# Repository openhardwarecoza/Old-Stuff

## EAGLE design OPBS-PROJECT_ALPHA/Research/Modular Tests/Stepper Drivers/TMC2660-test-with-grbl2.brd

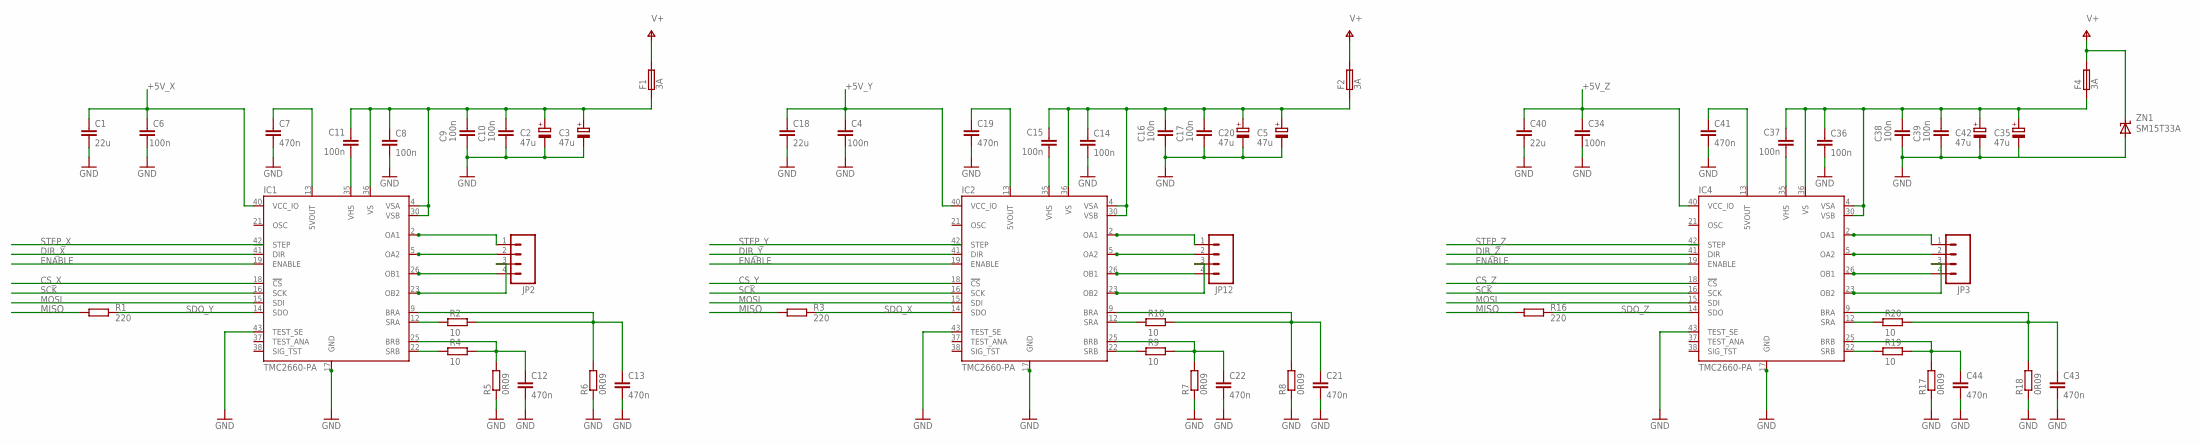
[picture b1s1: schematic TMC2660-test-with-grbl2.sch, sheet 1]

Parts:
C1, C18, C40: 22u; C1206; VOLTAGE 6.3V; PARTNR JMK316B7226ML-T
C2, C3, C5, C20, C35, C42: 47u; E5-8,5; VOLTAGE 50V; PARTNR EEEFK1H470XP
C4, C6, C34: 100n; C1206K; VOLTAGE 25V; PARTNR C0603C104K3RACTU
C7, C12, C13, C19, C21, C22, C41, C43, C44: 470n; 0805-WIDE; VOLTAGE 10V; PARTNR VJ0805Y474KXQTW1BC
C8, C9, C10, C11, C14, C15, C16, C17, C36, C37, C38, C39: 100n; C0603K; VOLTAGE 50V; PARTNR C0603C104K5RACTU
F1, F2, F4: 3A; AF2; VOLTAGE 125V; PARTNR CB61F3A-TR2
IC1, IC2, IC4: TMC2660-PA; PQFP44; PARTNR TMC2660
JP2, JP3, JP12: M04SCREW; SCREWTERMINAL-3.5MM-4
R1, R3, R16: 220; R0603; PARTNR SG73S1JTTD221J
R2, R4, R9, R10, R19, R20: 10; R0603; PARTNR RN73H1JTTD10R0F100
R5, R6, R7, R8, R17, R18: 0R09; R1206; PARTNR ERJ-B2CFR091V
ZN1: SM15T33A; SMC; PARTNR SM15T33A

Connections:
+5V_X: C1.1, C6.2, IC1.40 (VCC_IO)
+5V_Y: C4.2, C18.1, IC2.40 (VCC_IO)
+5V_Z: C34.2, C40.1, IC4.40 (VCC_IO)
CS_X: IC1.18 (!CS); also elsewhere on the board
CS_Y: IC2.18 (!CS); also elsewhere on the board
CS_Z: IC4.18 (!CS); also elsewhere on the board
DIR_X: IC1.41 (DIR); also elsewhere on the board
DIR_Y: IC2.41 (DIR); also elsewhere on the board
DIR_Z: IC4.41 (DIR); also elsewhere on the board
ENABLE: IC1.19 (ENABLE), IC2.19 (ENABLE), IC4.19 (ENABLE)
GND: C1.2, C2.-, C3.-, C4.1, C5.-, C6.1, C7.2, C8.2, C9.1, C10.1, C12.2, C13.2, C14.2, C16.1, C17.1, C18.2, C19.2, C20.-, C21.2, C22.2, C34.1, C35.-, C36.2, C38.1, C39.1, C40.2, C41.2, C42.-, C43.2, C44.2, IC1.17 (GND), IC1.39 (GND1), IC1.43 (TEST_SE), IC1.44 (GND2), IC2.17 (GND), IC2.39 (GND1), IC2.43 (TEST_SE), IC2.44 (GND2), IC4.17 (GND), IC4.39 (GND1), IC4.43 (TEST_SE), IC4.44 (GND2), R5.1, R6.1, R7.1, R8.1, R17.1, R18.1, ZN1.P$2 (A); also elsewhere on the board
MISO: R1.2, R3.2, R16.2; also elsewhere on the board
MOSI: IC1.15 (SDI), IC2.15 (SDI), IC4.15 (SDI); also elsewhere on the board
unnamed: IC1.22 (SRB), R4.2
unnamed: C12.1, IC1.25 (BRB), R4.1, R5.2
unnamed: C13.1, IC1.9 (BRA), R2.1, R6.2
unnamed: IC1.12 (SRA), R2.2
unnamed: C22.1, IC2.25 (BRB), R7.2, R9.1
unnamed: C21.1, IC2.9 (BRA), R8.2, R10.1
unnamed: IC2.22 (SRB), R9.2
unnamed: IC2.12 (SRA), R10.2
unnamed: C44.1, IC4.25 (BRB), R17.2, R19.1
unnamed: C43.1, IC4.9 (BRA), R18.2, R20.1
unnamed: IC4.22 (SRB), R19.2
unnamed: IC4.12 (SRA), R20.2
OA1: IC1.2 (OA1), IC1.3 (OA1_1), IC1.7 (OA1_2), IC1.8 (OA1_3), JP2.1
OA2: IC1.5 (OA2), IC1.6 (OA2_1), IC1.10 (OA2_2), IC1.11 (OA2_3), JP2.2
OA3: IC2.2 (OA1), IC2.3 (OA1_1), IC2.7 (OA1_2), IC2.8 (OA1_3), JP12.1
OA4: IC2.5 (OA2), IC2.6 (OA2_1), IC2.10 (OA2_2), IC2.11 (OA2_3), JP12.2
OA5: IC4.2 (OA1), IC4.3 (OA1_1), IC4.7 (OA1_2), IC4.8 (OA1_3), JP3.1
OA6: IC4.5 (OA2), IC4.6 (OA2_1), IC4.10 (OA2_2), IC4.11 (OA2_3), JP3.2
OB1: IC1.26 (OB1), IC1.27 (OB1_1), IC1.31 (OB1_2), IC1.32 (OB1_3), JP2.4
OB2: IC1.23 (OB2), IC1.24 (OB2_1), IC1.28 (OB2_2), IC1.29 (OB2_3), JP2.3
OB3: IC2.23 (OB2), IC2.24 (OB2_1), IC2.28 (OB2_2), IC2.29 (OB2_3), JP12.3
OB4: IC2.26 (OB1), IC2.27 (OB1_1), IC2.31 (OB1_2), IC2.32 (OB1_3), JP12.4
OB5: IC4.23 (OB2), IC4.24 (OB2_1), IC4.28 (OB2_2), IC4.29 (OB2_3), JP3.3
OB6: IC4.26 (OB1), IC4.27 (OB1_1), IC4.31 (OB1_2), IC4.32 (OB1_3), JP3.4
PWR_X: C2.+, C3.+, C8.1, C9.2, C10.2, C11.2, F1.P$1 (1), IC1.4 (VSA), IC1.30 (VSB), IC1.36 (VS)
PWR_Y: C5.+, C14.1, C15.2, C16.2, C17.2, C20.+, F2.P$1 (1), IC2.4 (VSA), IC2.30 (VSB), IC2.36 (VS)
PWR_Z: C35.+, C36.1, C37.2, C38.2, C39.2, C42.+, F4.P$1 (1), IC4.4 (VSA), IC4.30 (VSB), IC4.36 (VS)
SCK: IC1.16 (SCK), IC2.16 (SCK), IC4.16 (SCK); also elsewhere on the board
SDO_X: IC2.14 (SDO), R3.1
SDO_Y: IC1.14 (SDO), R1.1
SDO_Z: IC4.14 (SDO), R16.1
STEP_X: IC1.42 (STEP); also elsewhere on the board
STEP_Y: IC2.42 (STEP); also elsewhere on the board
STEP_Z: IC4.42 (STEP); also elsewhere on the board
V+: F1.P$2 (2), F2.P$2 (2), F4.P$2 (2), ZN1.P$1 (C); also elsewhere on the board
VHS: C11.1, IC1.35 (VHS)
VHS1: C15.1, IC2.35 (VHS)
VHS2: C37.1, IC4.35 (VHS)
VREG: C7.1, IC1.13 (5VOUT)
VREG1: C19.1, IC2.13 (5VOUT)
VREG2: C41.1, IC4.13 (5VOUT)

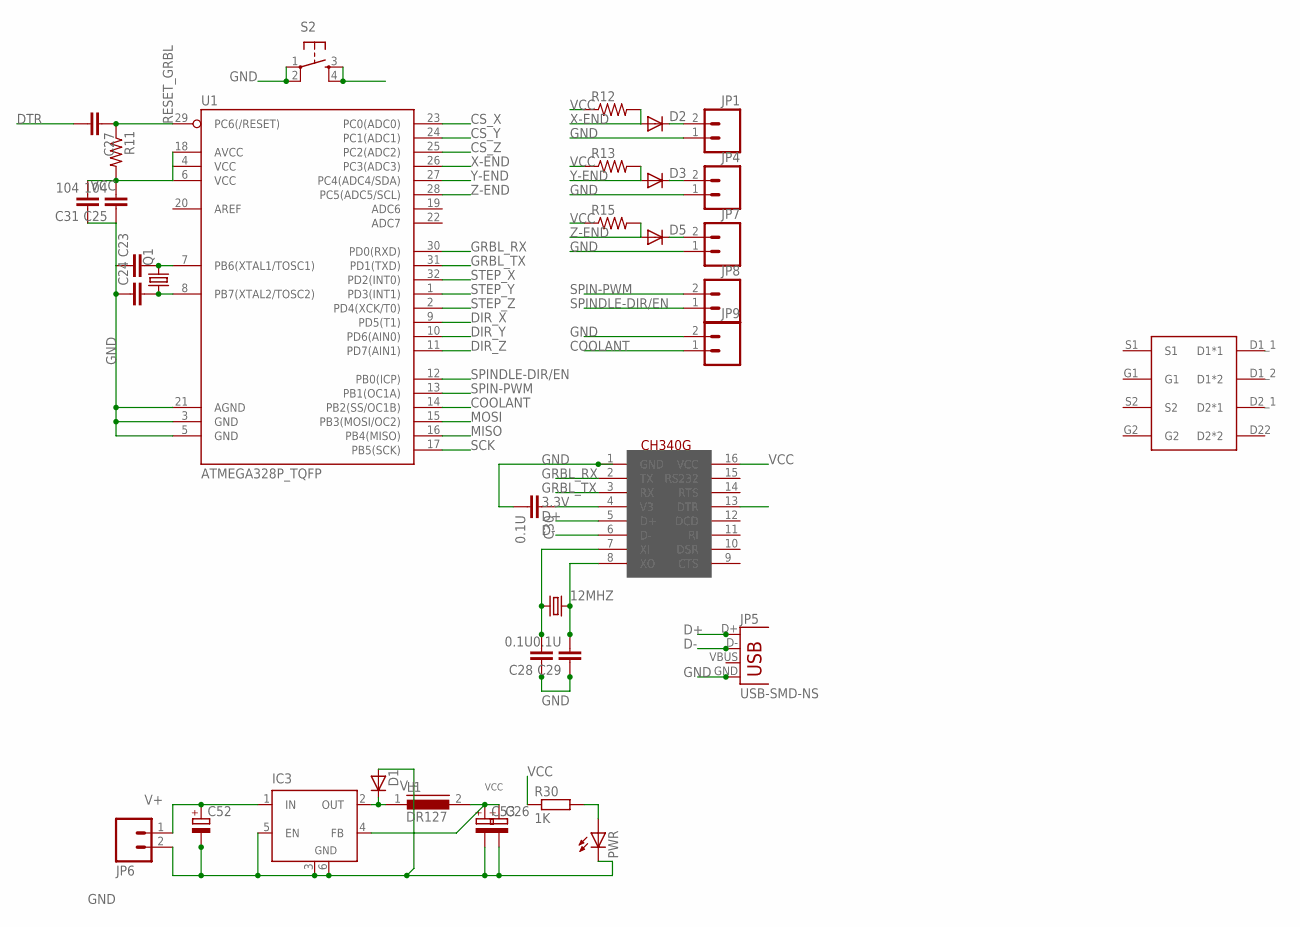
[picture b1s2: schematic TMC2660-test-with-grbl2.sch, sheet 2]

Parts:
12MHZ: CRYSTALHC49UP; HC49UP
C23, C24, C27: CAP1206; 1206
C25, C31: 104; 1206
C26: CPOL-EUE2.5-6; E2,5-6
C28, C29, C30: 0.1U; C1206
C52, C53: CPOL-EUE5-8.5; E5-8,5
D1: D-SOD-80; SOD80
D2, D3, D5: DIODESMB; SMB-DIODE
IC3: LM2596S; TO263-5
JP1, JP4, JP6, JP7, JP8, JP9: M023.5MM; SCREWTERMINAL-3.5MM-2
JP5: USB-SMD-NS; USB-MINIB-NOSTOP
L1: DR127
PWR: LEDCHIPLED_1206; CHIPLED_1206
Q1: CRYSTALHC49UP; HC49UP
R11, R12, R13, R15: RESISTOR1206; 1206
R30: 1K; M1206
S2: TAC_SWITCHSMD; TACTILE_SWITCH_SMD
U1: ATMEGA328P_TQFP; TQFP32-08
U$3: CSD88537ND
U$4: CH340G; SOIC16

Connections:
3.3V: C30.1, U$4.4 (V3)
COOLANT: JP9.1, U1.14 (PB2(SS/OC1B))
CS_X: U1.23 (PC0(ADC0)); also elsewhere on the board
CS_Y: U1.24 (PC1(ADC1)); also elsewhere on the board
CS_Z: U1.25 (PC2(ADC2)); also elsewhere on the board
D1*1: U$3.D1_1 (D1*1)
D1*2: U$3.D1_2 (D1*2)
D2*1: U$3.D2_1 (D2*1)
D2*2: U$3.D22 (D2*2)
D+: JP5.D+, U$4.5 (D+)
D-: JP5.D-, U$4.6 (D-)
DIR_X: U1.9 (PD5(T1)); also elsewhere on the board
DIR_Y: U1.10 (PD6(AIN0)); also elsewhere on the board
DIR_Z: U1.11 (PD7(AIN1)); also elsewhere on the board
DTR: C27.2, U$4.13 (DTR)
G1: U$3.G1
G2: U$3.G2
GND: C23.1, C24.1, C25.1, C26.-, C28.1, C29.1, C30.2, C31.1, C52.-, C53.-, D1.2 (A), IC3.3 (GND), IC3.5 (EN), IC3.6 (GND), JP1.1, JP4.1, JP5.GND, JP6.2, JP7.1, JP9.2, PWR.C, S2.1, S2.2, U1.3 (GND), U1.5 (GND), U1.21 (AGND), U$4.1 (GND); also elsewhere on the board
GRBL_RX: U1.30 (PD0(RXD)), U$4.2 (TX)
GRBL_TX: U1.31 (PD1(TXD)), U$4.3 (RX)
MISO: U1.16 (PB4(MISO)); also elsewhere on the board
MOSI: U1.15 (PB3(MOSI/OC2)); also elsewhere on the board
unnamed: C23.2, Q1.2, U1.7 (PB6(XTAL1/TOSC1))
unnamed: C24.2, Q1.1, U1.8 (PB7(XTAL2/TOSC2))
unnamed: D2.C, JP1.2
unnamed: D3.C, JP4.2
unnamed: 12MHZ.1, C28.2, U$4.7 (XI)
unnamed: D5.C, JP7.2
unnamed: 12MHZ.2, C29.2, U$4.8 (XO)
unnamed: D1.1 (C), IC3.2 (OUT), L1.1
unnamed: PWR.A, R30.2
RESET_GRBL: C27.1, R11.1, S2.3, S2.4, U1.29 (PC6(/RESET))
S1: U$3.S1
S2: U$3.S2
SCK: U1.17 (PB5(SCK)); also elsewhere on the board
SPIN-PWM: JP8.2, U1.13 (PB1(OC1A))
SPINDLE-DIR/EN: JP8.1, U1.12 (PB0(ICP))
STEP_X: U1.32 (PD2(INT0)); also elsewhere on the board
STEP_Y: U1.1 (PD3(INT1)); also elsewhere on the board
STEP_Z: U1.2 (PD4(XCK/T0)); also elsewhere on the board
V+: C52.+, IC3.1 (IN), JP6.1; also elsewhere on the board
VCC: C25.2, C26.+, C31.2, C53.+, IC3.4 (FB), L1.2, R11.2, R12.1, R13.1, R15.1, R30.1, U1.4 (VCC), U1.6 (VCC), U1.18 (AVCC), U$4.16 (VCC)
X-END: D2.A, R12.2, U1.26 (PC3(ADC3))
Y-END: D3.A, R13.2, U1.27 (PC4(ADC4/SDA))
Z-END: D5.A, R15.2, U1.28 (PC5(ADC5/SCL))

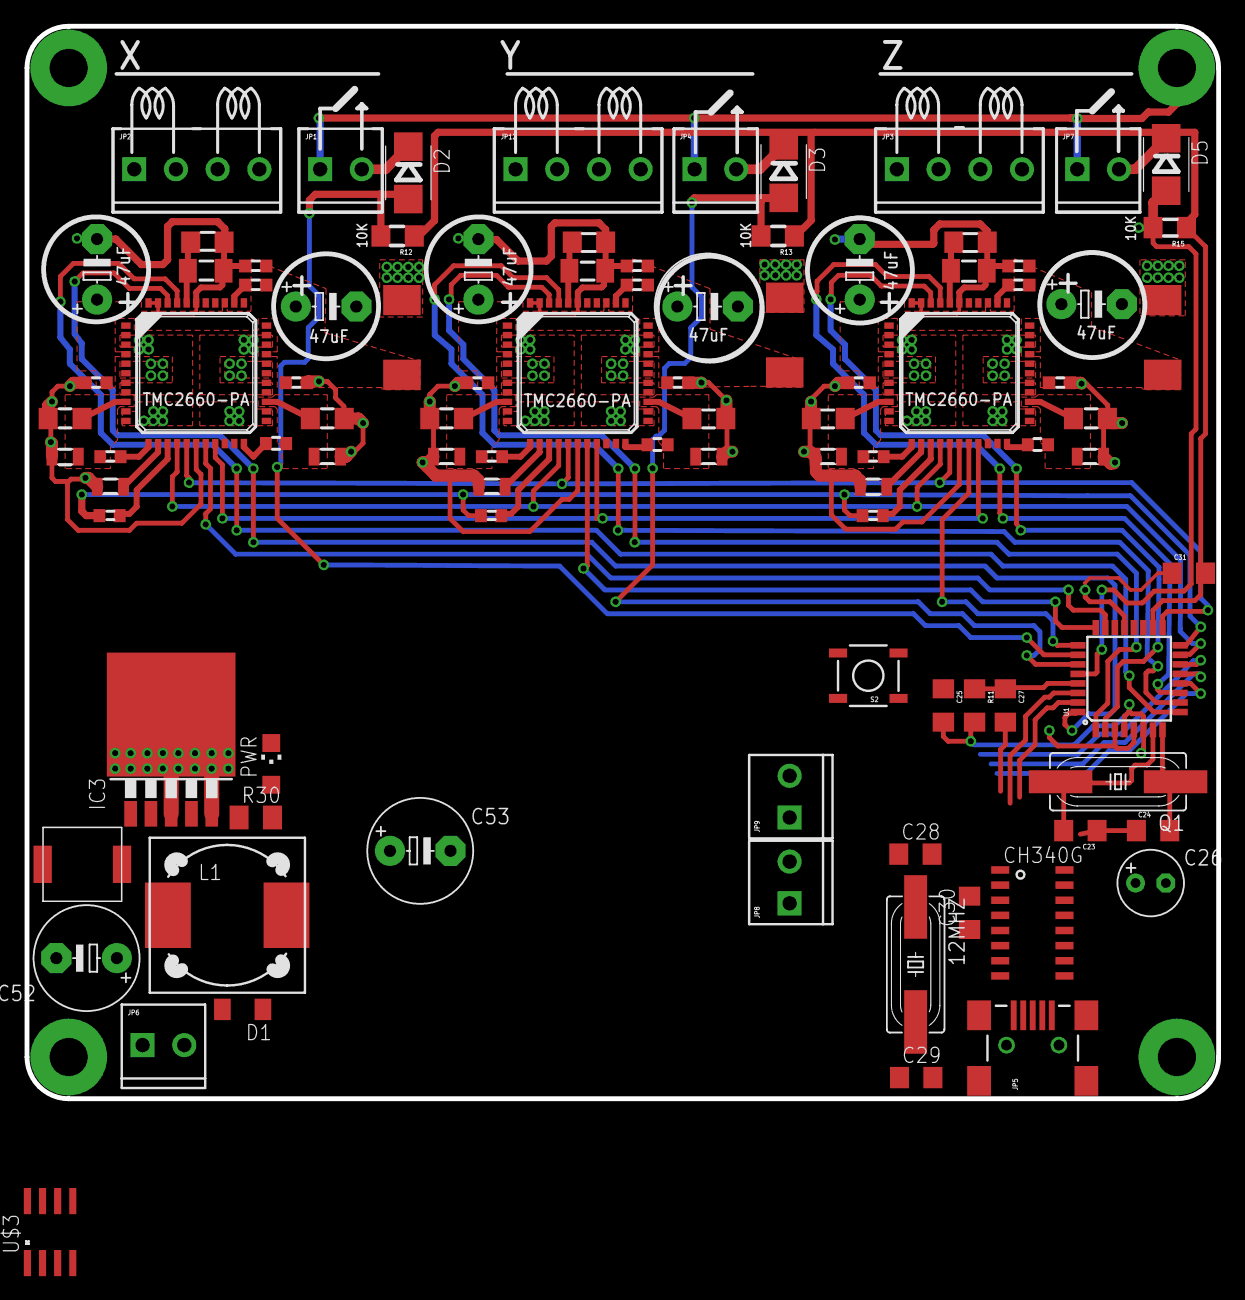
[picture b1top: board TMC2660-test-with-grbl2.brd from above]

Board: 2 copper layers, 100.0 x 90.0 mm, 94 parts (0 on the bottom side), 77 nets.

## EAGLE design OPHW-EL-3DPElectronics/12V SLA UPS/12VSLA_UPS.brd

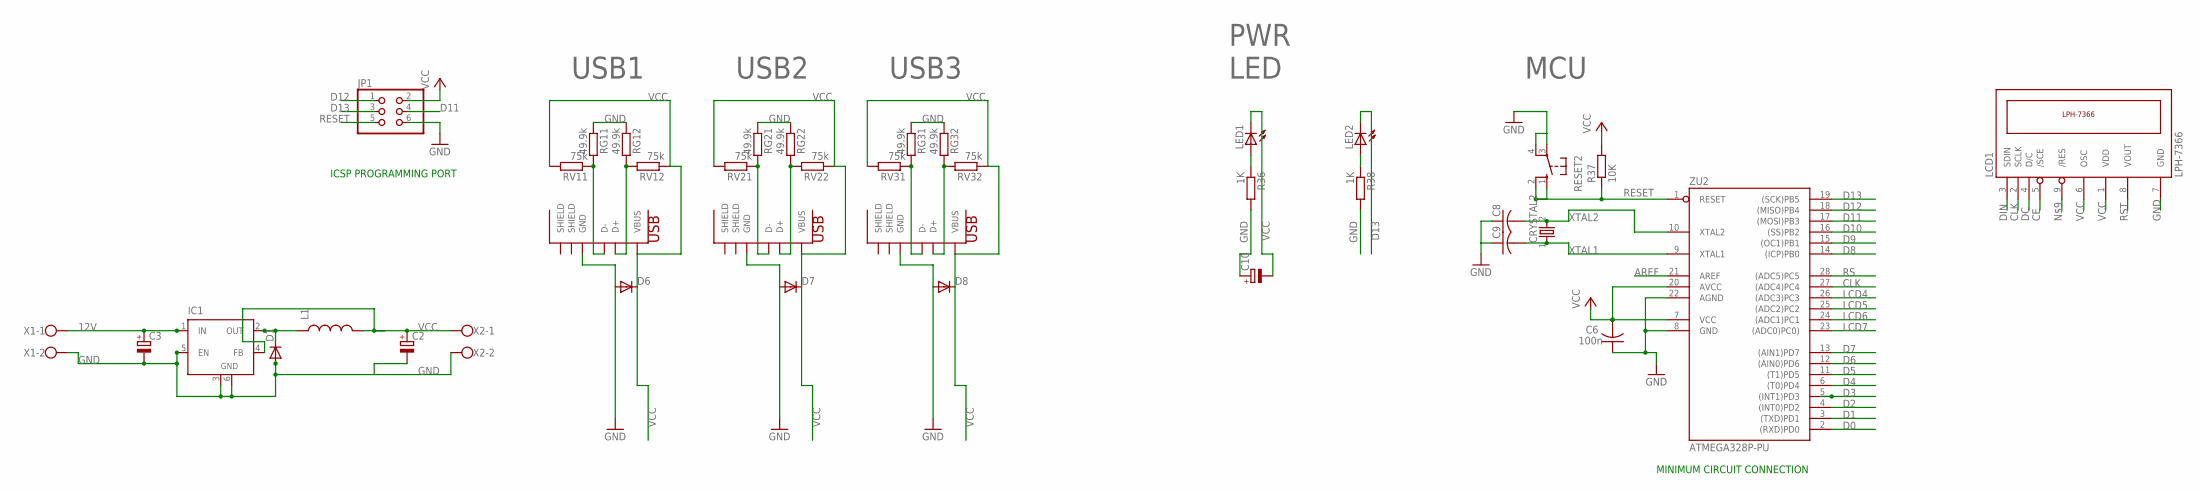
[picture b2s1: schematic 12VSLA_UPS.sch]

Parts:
C2, C3: CPOL-EU153CLV-0605; 153CLV-0605
C6: 100n; C1206K
C8, C9: C-USC1206K; C1206K
C10: CPOL-EU153CLV-0807; 153CLV-0807
CRYSTAL2: CRYSTAL2PIN; CRYSTAL-2PIN
D1: DIODE-DO-214AC; DO-214AC
D6, D7, D8: DIODESMA-ALT; SMA-DIODE_ALT
IC1: LM2596S; TO263-5
JP1: PINHD-2X3; 2X03
L1: INDUCTORPWR; CDRH125
LCD1: LPH-7366
LED1, LED2: LED3MM
R36, R38: 1K; M1206
R37: 10K; M1206
RESET2: 10-XX; B3F-10XX
RG11, RG12, RG21, RG22, RG31, RG32: 49.9k; M1206
RV11, RV12, RV21, RV22, RV31, RV32: 75k; M1206
USB1, USB2, USB3: USB-A-H
X1, X2: W237-102
ZU2: ATMEGA328P-PU; DIL28-3

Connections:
12V: C3.+, IC1.1 (IN), X1.1
AREF: ZU2.21 (AREF)
CE: LCD1.5 (/SCE)
CLK: LCD1.2 (SCLK), ZU2.27 ((ADC4)PC4)
D0: ZU2.2 ((RXD)PD0)
D1: ZU2.3 ((TXD)PD1)
D2: ZU2.4 ((INT0)PD2)
D3: ZU2.5 ((INT1)PD3)
D4: ZU2.6 ((T0)PD4)
D5: ZU2.11 ((T1)PD5)
D6: ZU2.12 ((AIN0)PD6)
D7: ZU2.13 ((AIN1)PD7)
D8: ZU2.14 ((ICP)PB0)
D9: ZU2.15 ((OC1)PB1)
D10: ZU2.16 ((SS)PB2)
D11: JP1.4, ZU2.17 ((MOSI)PB3)
D12: JP1.1, ZU2.18 ((MISO)PB4)
D13: JP1.3, LED2.K (C), ZU2.19 ((SCK)PB5)
D+4: RG12.2, RV12.2, USB1.D+
D+5: RG22.2, RV22.2, USB2.D+
D+6: RG32.2, RV32.2, USB3.D+
D-4: RG11.2, RV11.1, USB1.D-
D-5: RG21.2, RV21.1, USB2.D-
D-6: RG31.2, RV31.1, USB3.D-
DC: LCD1.4 (D/C)
DIN: LCD1.3 (SDIN)
GND: C2.-, C3.-, C6.1, C8.1, C9.1, C10.+, D1.2 (A), D6.A, D7.A, D8.A, IC1.3 (GND), IC1.5 (EN), IC1.6 (GND), JP1.6, LCD1.7 (GND), R36.2, R38.2, RESET2.3, RESET2.4 (P1), RG11.1, RG12.1, RG21.1, RG22.1, RG31.1, RG32.1, USB1.GND, USB2.GND, USB3.GND, X1.2, X2.2, ZU2.8 (GND), ZU2.22 (AGND)
LCD4: ZU2.26 ((ADC3)PC3)
LCD5: ZU2.25 ((ADC2)PC2)
LCD6: ZU2.24 ((ADC1)PC1)
LCD7: ZU2.23 ((ADC0)PC0))
unnamed: D1.1 (C), IC1.2 (OUT), L1.1
unnamed: LED1.A, R36.1
unnamed: LED2.A, R38.1
RESET: JP1.5, R37.1, RESET2.1 (S), RESET2.2 (S1), ZU2.1 (RESET)
RS: ZU2.28 ((ADC5)PC5)
RST: LCD1.8 (VOUT)
VCC: C2.+, C6.2, C10.-, D6.C, D7.C, D8.C, IC1.4 (FB), JP1.2, L1.2, LCD1.1 (VDD), LCD1.6 (OSC), LED1.K (C), R37.2, RV11.2, RV12.1, RV21.2, RV22.1, RV31.2, RV32.1, USB1.VBUS, USB2.VBUS, USB3.VBUS, X2.1, ZU2.7 (VCC), ZU2.20 (AVCC)
XTAL1: C9.2, CRYSTAL2.1, ZU2.9 (XTAL1)
XTAL2: C8.2, CRYSTAL2.2, ZU2.10 (XTAL2)

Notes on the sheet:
USB1
USB2
USB3
PWR LED
ICSP PROGRAMMING PORT
MINIMUM CIRCUIT CONNECTION
MCU

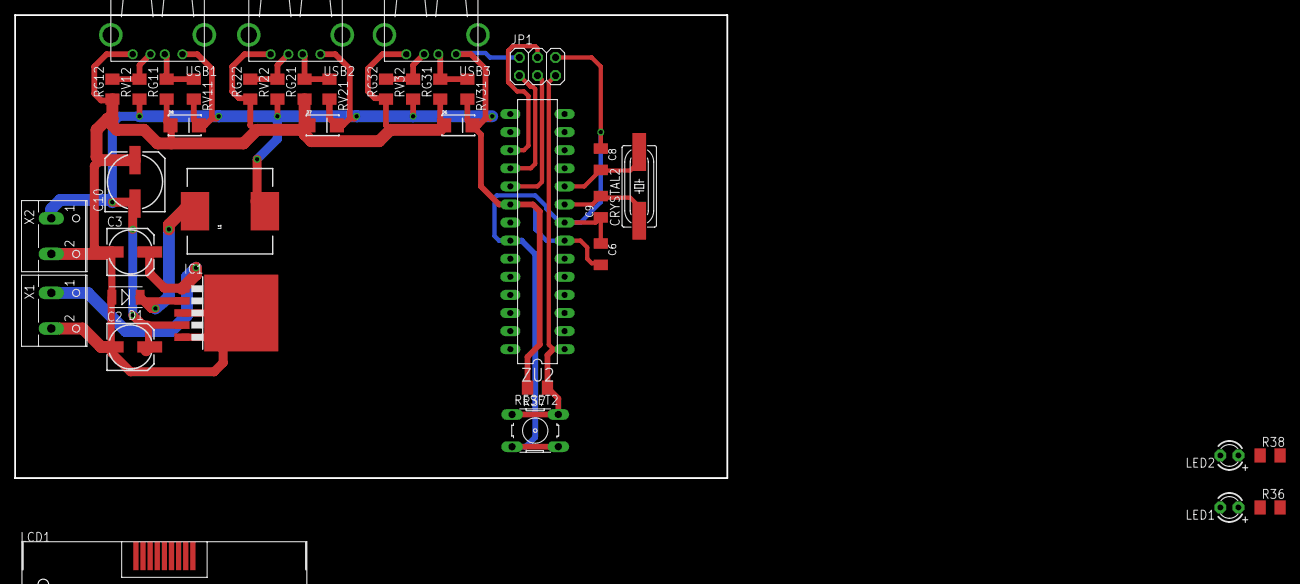
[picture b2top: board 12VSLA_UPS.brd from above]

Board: 2 copper layers, 100.0 x 65.0 mm, 39 parts (0 on the bottom side), 19 nets.

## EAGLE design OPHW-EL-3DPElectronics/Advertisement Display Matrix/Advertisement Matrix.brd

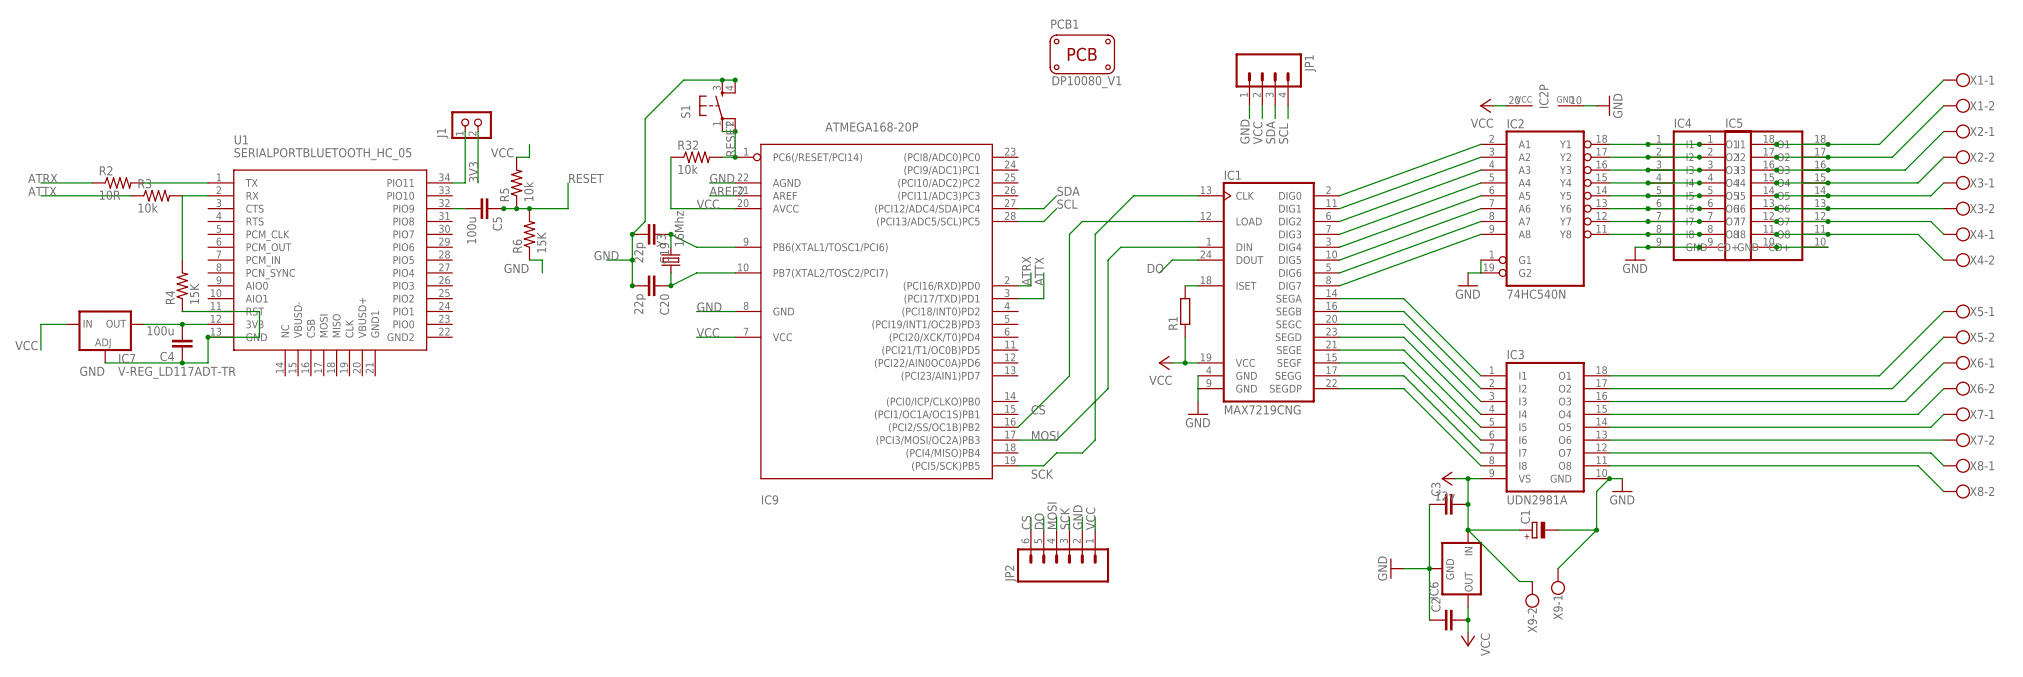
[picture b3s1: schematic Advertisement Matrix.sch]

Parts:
C1: CPOL-EUE2.5-7; E2,5-7
C2, C3: C-EUC1206K; C1206K
C4, C5: 100u; 1206
C19, C20: 22p; 1206
IC1: MAX7219CNG; DIL24-3
IC2: 74HC540N; DIL20
IC3: UDN2981A; DIL18
IC4, IC5: IC_ULN2803AN; DIL18
IC6: 78XXL
IC7: V-REG_LD117ADT-TR; V-REG_DPACK
IC9: ATMEGA168-20P; DIL28-3
J1: CON_HEADER_1X02-PTH; M1X2
JP1: M04POLAR_LOCK; MOLEX-1X4_LOCK
JP2: M06POLAR_LOCK; MOLEX-1X6_LOCK
PCB1: PCB_DP_RECTANGLE-80X100; DP10080_V1
R1: R-EU_0207/7; 0207/7
R2: 10R; M1206
R3, R5, R32: 10k; M1206
R4, R6: 15K; M1206
S1: TAC_SWITCHPTH; TACTILE-PTH
U1: SERIALPORTBLUETOOTH_HC_05; SERIALPORTBLUETOOTH_BLUETOOTH_SMD
X1, X2, X3, X4, X5, X6, X7, X8, X9: W237-102
Y3: 16Mhz; HC49UP

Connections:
3V3: C4.2, IC7.4 (OUT), J1.2, U1.12 (3V3)
12V: C1.+, C3.2, IC3.9 (VS), IC6.IN, X9.2
AREF2: IC9.21 (AREF)
ATRX: IC9.2 ((PCI16/RXD)PD0), R2.1
ATTX: IC9.3 ((PCI17/TXD)PD1), R3.1
CS: IC1.12 (LOAD), IC9.16 ((PCI2/SS/OC1B)PB2), JP2.6
DO: IC1.24 (DOUT), JP2.5
GND: C1.-, C2.1, C3.1, C4.1, C19.2, C20.2, IC1.4 (GND), IC1.9 (GND), IC2.1 (G1), IC2.10 (GND), IC2.19 (G2), IC3.10 (GND), IC4.9 (GND), IC5.9 (GND), IC6.GND, IC7.1 (ADJ), IC9.8 (GND), IC9.22 (AGND), JP1.1, JP2.2, R4.1, R6.1, S1.3, S1.4, U1.13 (GND), X9.1
MOSI: IC1.1 (DIN), IC9.17 ((PCI3/MOSI/OC2A)PB3), JP2.4
unnamed: IC1.2 (DIG0), IC2.2 (A1)
unnamed: IC1.11 (DIG1), IC2.3 (A2)
unnamed: IC1.6 (DIG2), IC2.4 (A3)
unnamed: IC1.7 (DIG3), IC2.5 (A4)
unnamed: IC1.3 (DIG4), IC2.6 (A5)
unnamed: IC1.10 (DIG5), IC2.7 (A6)
unnamed: IC1.5 (DIG6), IC2.8 (A7)
unnamed: IC1.8 (DIG7), IC2.9 (A8)
unnamed: IC1.14 (SEGA), IC3.1 (I1)
unnamed: IC1.16 (SEGB), IC3.2 (I2)
unnamed: IC1.20 (SEGC), IC3.3 (I3)
unnamed: IC1.23 (SEGD), IC3.4 (I4)
unnamed: IC1.21 (SEGE), IC3.5 (I5)
unnamed: IC1.15 (SEGF), IC3.6 (I6)
unnamed: IC1.17 (SEGG), IC3.7 (I7)
unnamed: IC1.22 (SEGDP), IC3.8 (I8)
unnamed: IC2.18 (Y1), IC4.1 (I1), IC5.1 (I1)
unnamed: IC2.17 (Y2), IC4.2 (I2), IC5.2 (I2)
unnamed: IC2.16 (Y3), IC4.3 (I3), IC5.3 (I3)
unnamed: IC2.15 (Y4), IC4.4 (I4), IC5.4 (I4)
unnamed: IC2.14 (Y5), IC4.5 (I5), IC5.5 (I5)
unnamed: IC2.13 (Y6), IC4.6 (I6), IC5.6 (I6)
unnamed: IC2.12 (Y7), IC4.7 (I7), IC5.7 (I7)
unnamed: IC2.11 (Y8), IC4.8 (I8), IC5.8 (I8)
unnamed: IC3.18 (O1), X5.1
unnamed: IC3.17 (O2), X5.2
unnamed: IC3.16 (O3), X6.1
unnamed: IC3.15 (O4), X6.2
unnamed: IC3.14 (O5), X7.1
unnamed: IC3.13 (O6), X7.2
unnamed: IC3.12 (O7), X8.1
unnamed: IC3.11 (O8), X8.2
unnamed: IC4.10 (CD+), IC5.10 (CD+)
unnamed: IC4.11 (O8), IC5.11 (O8), X4.2
unnamed: IC4.12 (O7), IC5.12 (O7), X4.1
unnamed: IC4.13 (O6), IC5.13 (O6), X3.2
unnamed: IC4.14 (O5), IC5.14 (O5), X3.1
unnamed: IC4.15 (O4), IC5.15 (O4), X2.2
unnamed: IC4.16 (O3), IC5.16 (O3), X2.1
unnamed: IC4.17 (O2), IC5.17 (O2), X1.2
unnamed: IC4.18 (O1), IC5.18 (O1), X1.1
unnamed: IC1.18 (ISET), R1.2
unnamed: R2.2, U1.1 (TX)
unnamed: R3.2, R4.2, U1.2 (RX)
unnamed: J1.1, U1.34 (PIO11)
unnamed: C5.2, U1.32 (PIO9)
RESET: C5.1, IC9.1 (PC6(/RESET/PCI14)), R5.1, R6.2, R32.2, S1.1, S1.2
SCK: IC1.13 (CLK), IC9.19 ((PCI5/SCK)PB5), JP2.3
SCL: IC9.28 ((PCI13/ADC5/SCL)PC5), JP1.4
SDA: IC9.27 ((PCI12/ADC4/SDA)PC4), JP1.3
VCC: C2.2, IC1.19 (VCC), IC2.20 (VCC), IC6.OUT, IC7.3 (IN), IC9.7 (VCC), IC9.20 (AVCC), JP1.2, JP2.1, R1.1, R5.2, R32.1
XTAL5: C20.1, IC9.10 (PB7(XTAL2/TOSC2/PCI7)), Y3.1
XTAL6: C19.1, IC9.9 (PB6(XTAL1/TOSC1/PCI6)), Y3.2

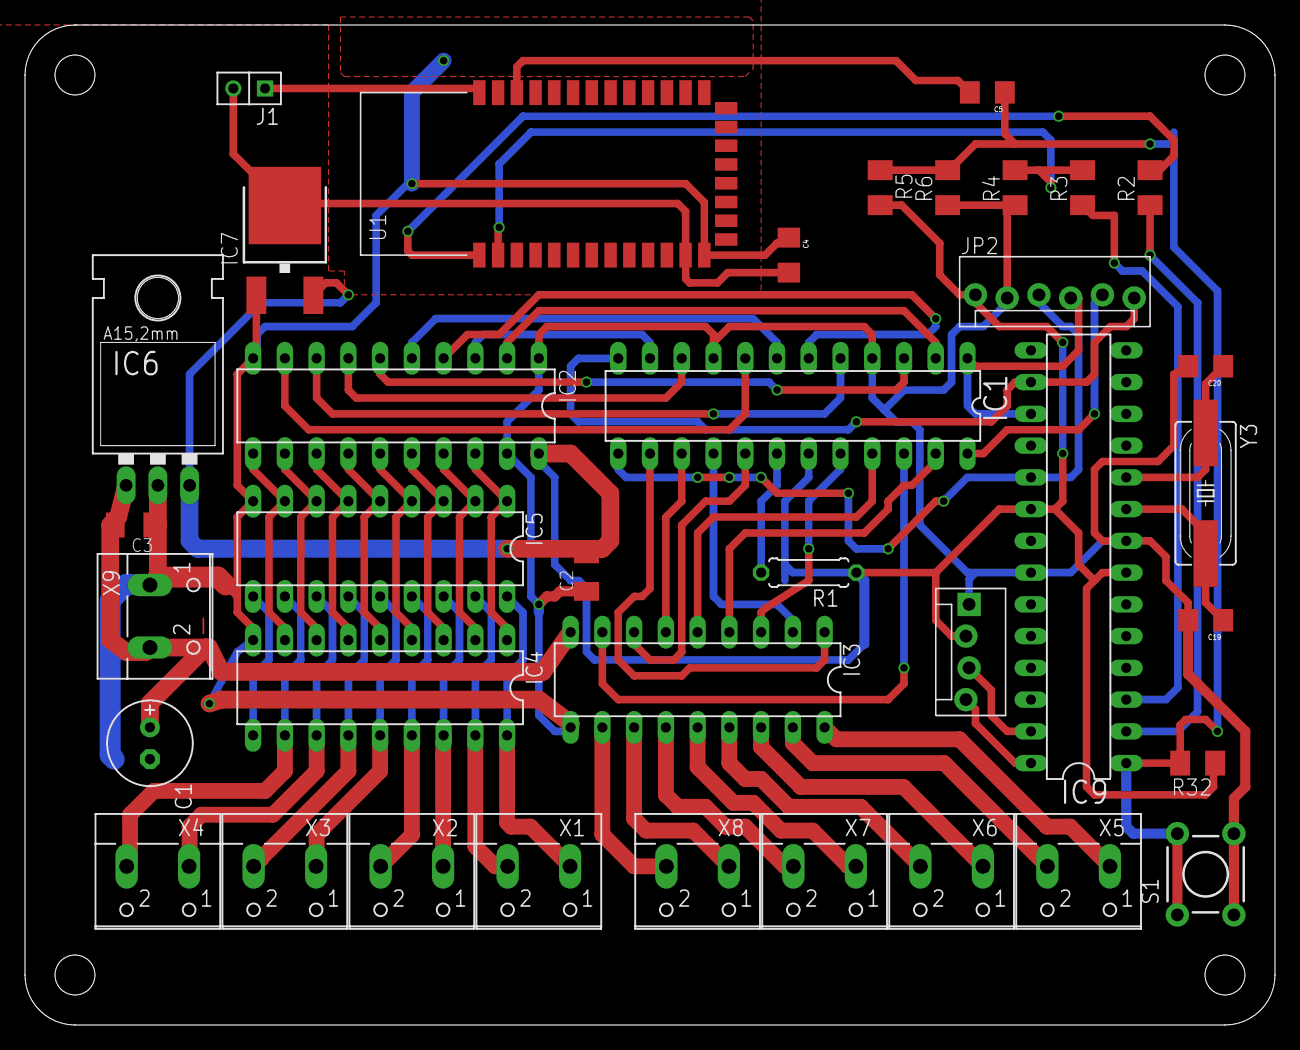
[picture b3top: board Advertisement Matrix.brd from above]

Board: 2 copper layers, 100.0 x 80.0 mm, 38 parts (0 on the bottom side), 61 nets.

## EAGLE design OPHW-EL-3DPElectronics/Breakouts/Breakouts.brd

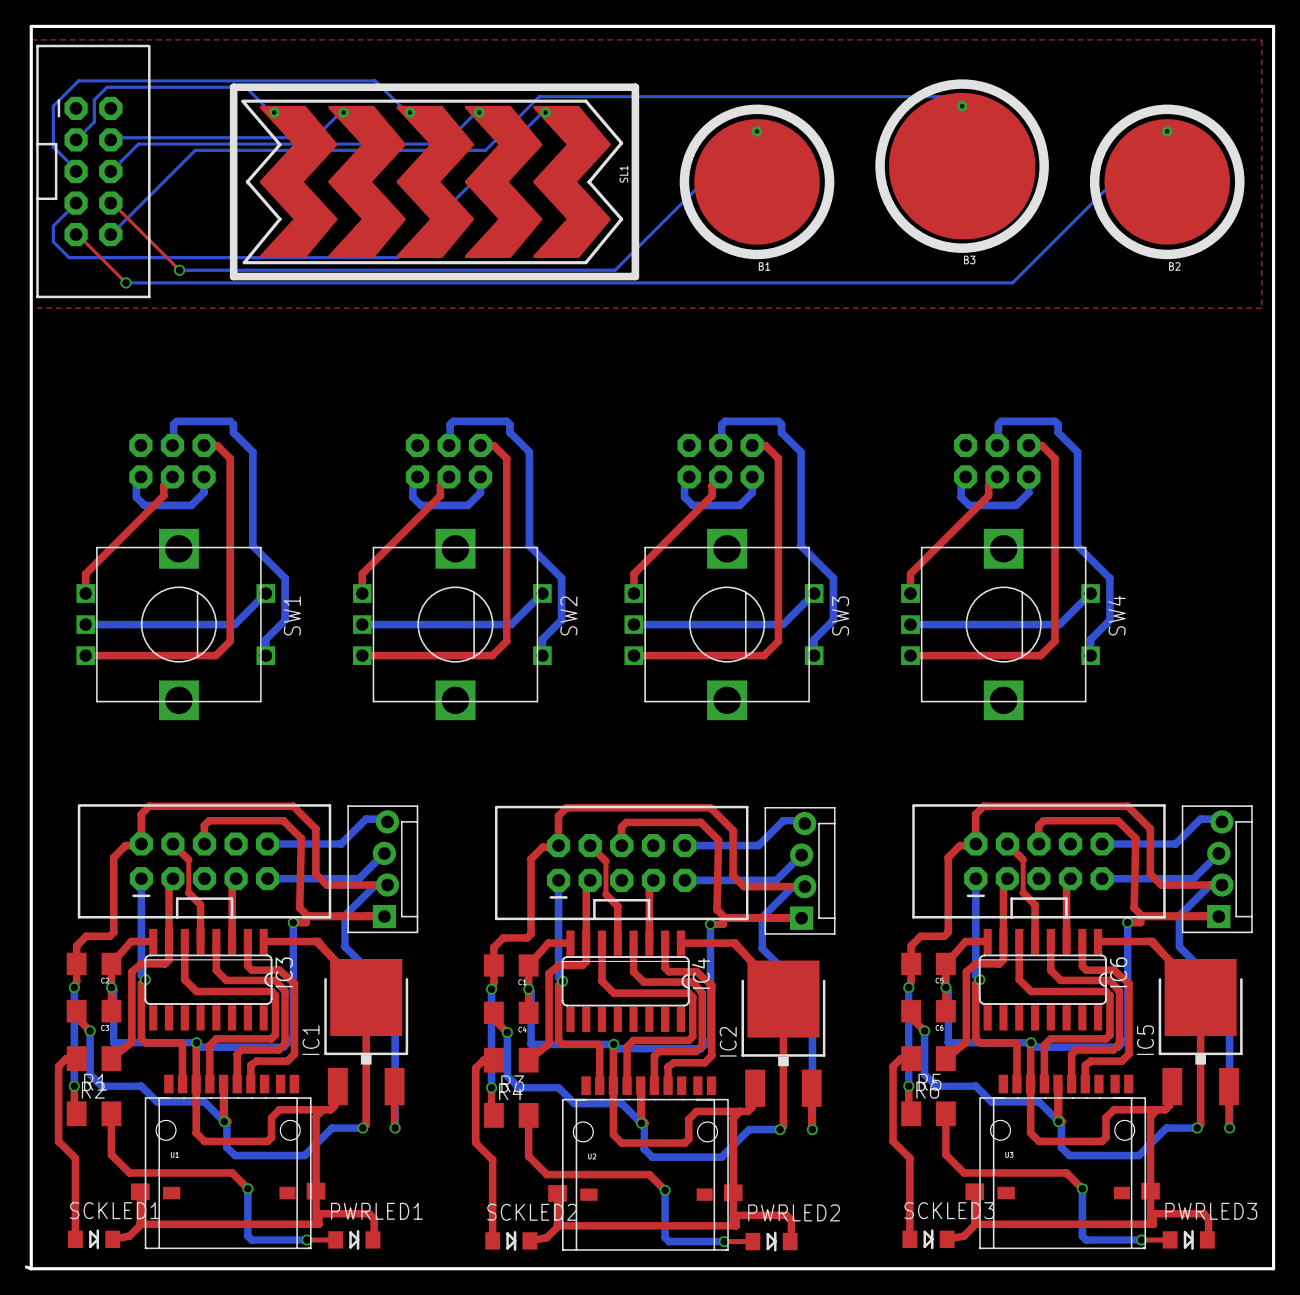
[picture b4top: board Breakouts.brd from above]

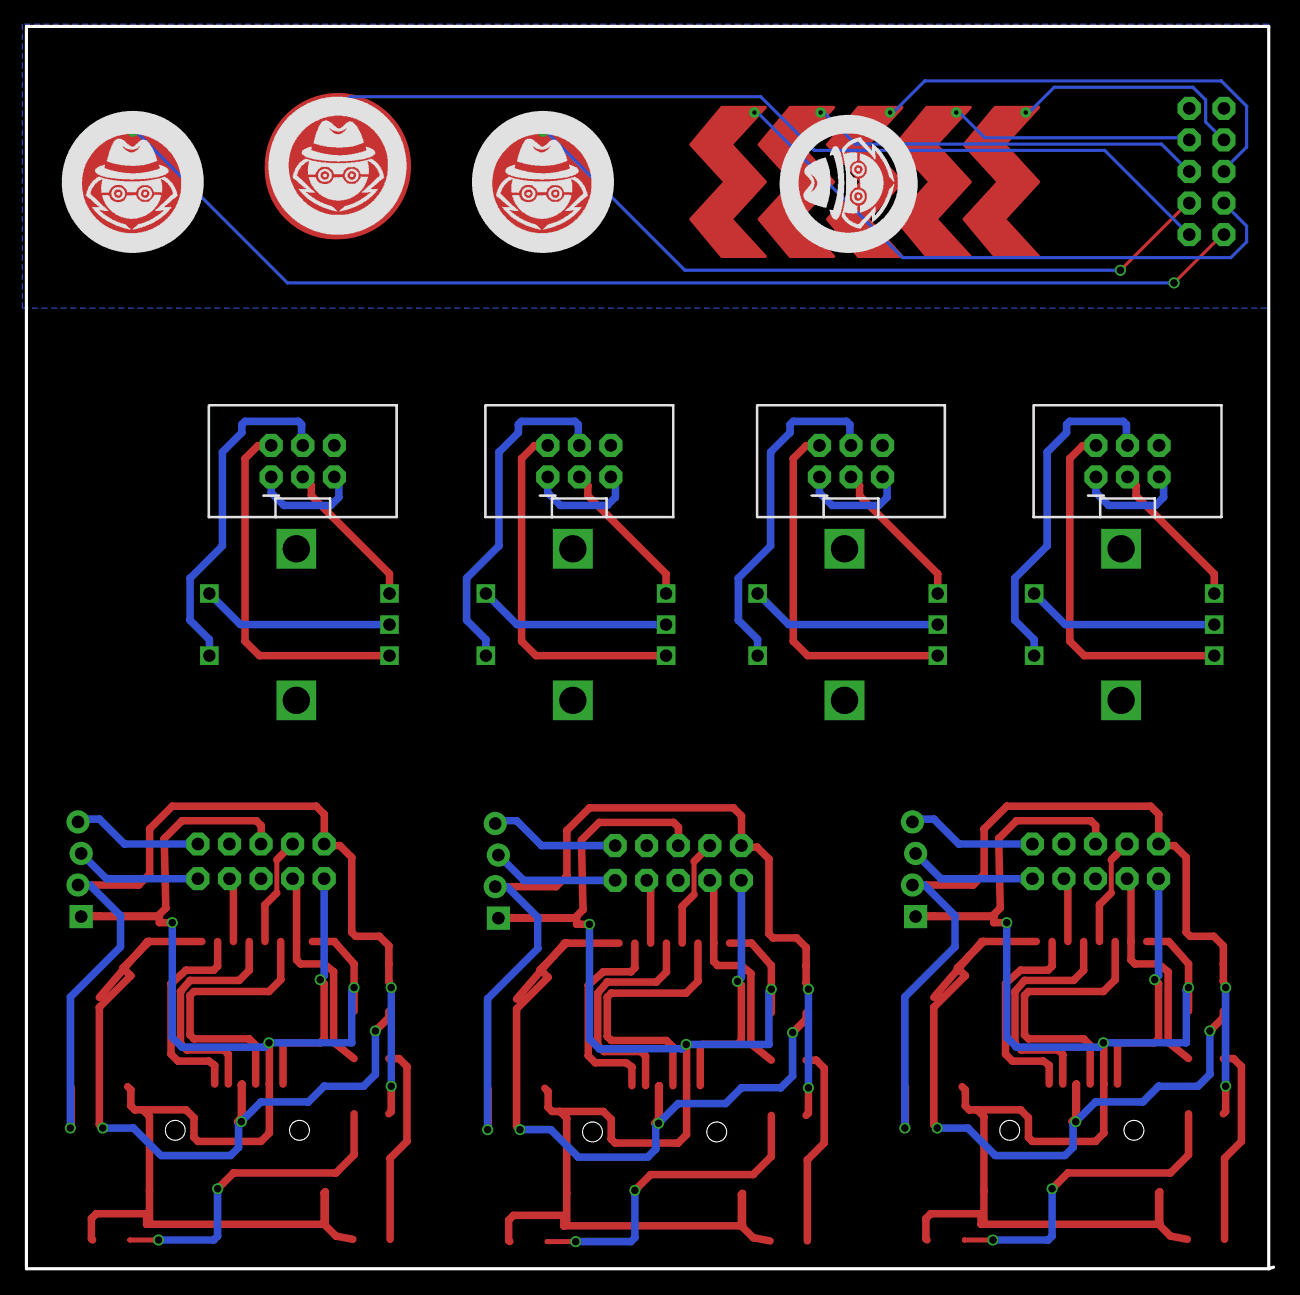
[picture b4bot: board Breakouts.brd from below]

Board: 2 copper layers, 100.0 x 100.0 mm, 46 parts (4 on the bottom side), 69 nets.

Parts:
B1, B2: BUTTON_PASSIVE_10MM
B3: BUTTON_PASSIVE_12MM
C1, C2, C3, C4, C5, C6: 0.1u; 1206
IC1, IC2, IC5: LD117ADT-TR; DPACK
IC3, IC4, IC6: 4050D; SO16
JP1, JP4, JP6, JP11: M05X2SHD_LOCK; 2X5-SHROUDED_LOCK
JP2, JP8, JP9, JP10: 2X3-SHROUDED
JP3, JP5, JP7: MOLEX-1X4_LOCK
PWRLED1, PWRLED2, PWRLED3: LED-1206
R1, R2, R3, R4, R5, R6: M1206
SCKLED1, SCKLED2, SCKLED3: LED-1206
SL1: SLIDER_PASSIVE_5SEG; SLIDER_PASSIVE_5SEG_12MM
SW1, SW2, SW3, SW4: EC12E_SW; ALPS_EC12E_SW
U1, U2, U3: USD-SOCKETUSD; USD-SOCKET-PP

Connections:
3V3SD: C3.2, IC1.4, IC3.1, U1.4
3V3SD1: C4.2, IC2.4, IC4.1, U2.4
3V3SD2: C6.2, IC5.4, IC6.1, U3.4
B1: B1.BUTTON, JP11.8
B2: B2.BUTTON, JP11.9
B3: B3.BUTTON, JP11.10
CS: IC3.2, U1.2
CS1: IC4.2, U2.2
CS2: IC6.2, U3.2
DI: IC3.4, U1.3
DI1: IC4.4, U2.3
DI2: IC6.4, U3.3
ENCA: JP2.2, SW1.B
ENCA1: JP8.2, SW2.B
ENCA2: JP9.2, SW3.B
ENCA3: JP10.2, SW4.B
ENCB: JP2.3, SW1.A
ENCB1: JP8.3, SW2.A
ENCB2: JP9.3, SW3.A
ENCB3: JP10.3, SW4.A
ENCC: JP2.4, SW1.E
ENCC1: JP8.4, SW2.E
ENCC2: JP9.4, SW3.E
ENCC3: JP10.4, SW4.E
GND: C2.1, C3.1, IC1.1, IC3.8, JP1.6, JP2.1, JP2.5, JP3.1, PWRLED1.C, SCKLED1.C, U1.6, U1.GND1, U1.GND2
GND1: C1.1, C4.1, IC2.1, IC4.8, JP4.6, JP5.1, PWRLED2.C, SCKLED2.C, U2.6, U2.GND1, U2.GND2
GND2: C5.1, C6.1, IC5.1, IC6.8, JP6.6, JP7.1, PWRLED3.C, SCKLED3.C, U3.6, U3.GND1, U3.GND2
GND3: JP8.1, JP8.5
GND4: JP9.1, JP9.5
GND5: JP10.1, JP10.5
MISO: JP1.1, U1.7
MISO1: JP4.1, U2.7
MISO2: JP6.1, U3.7
MOSI: IC3.5, JP1.4
MOSI1: IC4.5, JP4.4
MOSI2: IC6.5, JP6.4
unnamed: SW1.C, SW1.D
unnamed: R1.2, SCKLED1.A
unnamed: PWRLED1.A, R2.2
unnamed: R3.2, SCKLED2.A
unnamed: PWRLED2.A, R4.2
unnamed: R5.2, SCKLED3.A
unnamed: PWRLED3.A, R6.2
unnamed: SW2.C, SW2.D
unnamed: SW3.C, SW3.D
unnamed: SW4.C, SW4.D
SC: IC3.6, U1.5
SC1: IC4.6, U2.5
SC2: IC6.6, U3.5
SCK: IC3.7, JP1.3, R1.1
SCK1: IC4.7, JP4.3, R3.1
SCK2: IC6.7, JP6.3, R5.1
SCL: JP1.10, JP3.4
SCL1: JP4.10, JP5.4
SCL2: JP6.10, JP7.4
SDA: JP1.9, JP3.3
SDA1: JP4.9, JP5.3
SDA2: JP6.9, JP7.3
SDS: IC3.3, JP1.7
SDS1: IC4.3, JP4.7
SDS2: IC6.3, JP6.7
SL1: JP11.3, SL1.SL1
SL2: JP11.4, SL1.SL2
SL3: JP11.5, SL1.SL3
SL4: JP11.6, SL1.SL4
SL5: JP11.7, SL1.SL5
VCC: C2.2, IC1.3, JP1.2, JP2.6, JP3.2, R2.1
VCC1: C1.2, IC2.3, JP4.2, JP5.2, R4.1
VCC2: C5.2, IC5.3, JP6.2, JP7.2, R6.1

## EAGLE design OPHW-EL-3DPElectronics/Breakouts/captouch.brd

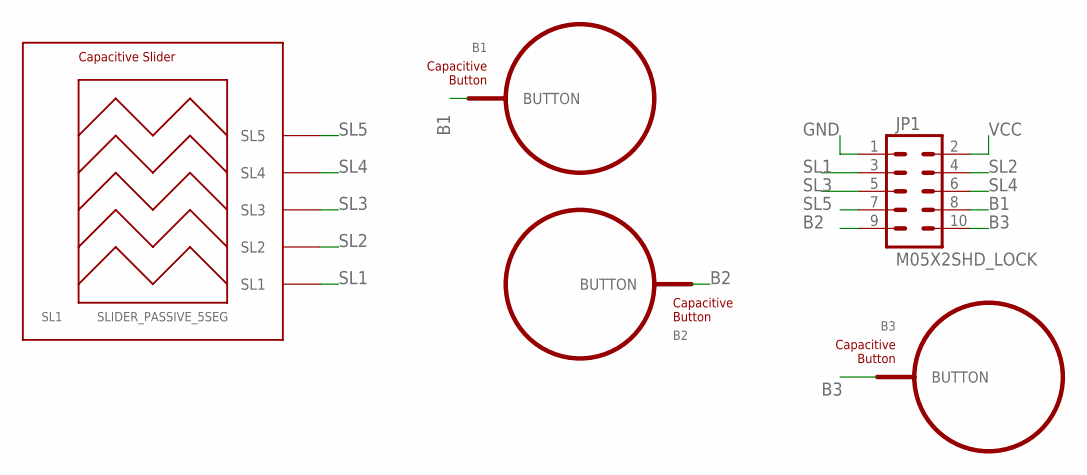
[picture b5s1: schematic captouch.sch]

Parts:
B1, B2: BUTTON_PASSIVE10MM; BUTTON_PASSIVE_10MM
B3: BUTTON_PASSIVE12MM; BUTTON_PASSIVE_12MM
JP1: M05X2SHD_LOCK; 2X5-SHROUDED_LOCK
SL1: SLIDER_PASSIVE_5SEG; SLIDER_PASSIVE_5SEG_12MM

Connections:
B1: B1.BUTTON, JP1.8
B2: B2.BUTTON, JP1.9
B3: B3.BUTTON, JP1.10
GND: JP1.1
SL1: JP1.3, SL1.SL1
SL2: JP1.4, SL1.SL2
SL3: JP1.5, SL1.SL3
SL4: JP1.6, SL1.SL4
SL5: JP1.7, SL1.SL5
VCC: JP1.2

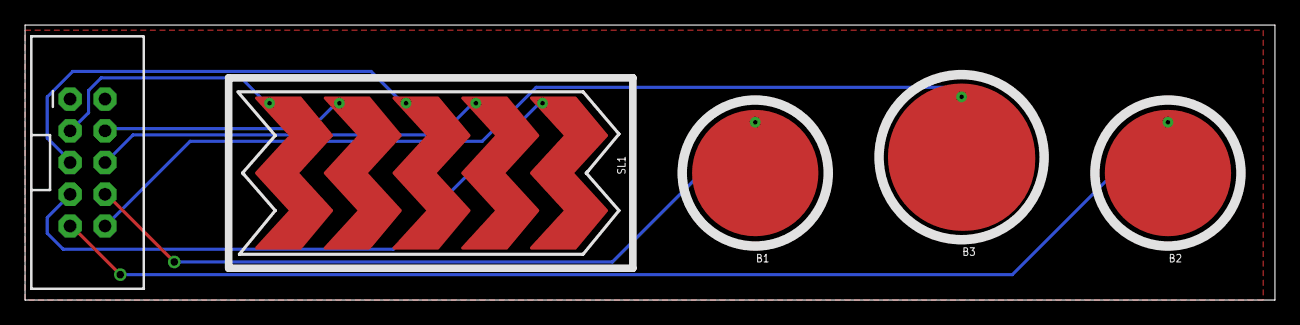
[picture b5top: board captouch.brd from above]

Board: 2 copper layers, 100.0 x 22.0 mm, 5 parts (0 on the bottom side), 8 nets.

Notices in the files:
OPHW-EL-3DPElectronics/Advertisement Display Matrix/Advertisement Matrix.brd:
CC-BY-SA
parts and their libraries:
02_eigene: Konrad Meyer (c) 2011
SparkFun-DigitalIC: Licensing: Creative Commons ShareAlike 4.0 International - https://creativecommons.org/licenses/by-sa/4.0
SparkFun-Connectors: Licensing: CC v3.0 Share-Alike You are welcome to use this library for commercial purposes.
